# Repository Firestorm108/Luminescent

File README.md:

# Luminescent

A 60W handheld portal gun based on industrial surplus I acquired off eBay. I use a very high power laser diode array that is from industrial laser modules for purposes like copper treatment. It has a fully custom board that manages constant current regulation and battery management.
It fits inside a 3D printable portal gun with a voltmeter, safety, and trigger. 

<h1>Laser Safety</h1>

** Make sure to ALWAYS buy laser goggles from a reputable brand and with properly rated specifications. **

** Lasers are extremely dangerous and you should never look at them directly and always wear proper safety goggles. **

** I am not responsible for any damage caused from irresponsibly using lasers. ** 

**General Tips for Working with Lasers:**

* The glasses that come with lasers are NOT safe, and will not protect your eyes.

* Lasers over 5mW require proper laser goggles, 5mW is still dangerous however the blink reflex protects you in most cases.

* Cutting with lasers releases fumes which need to be filtered or ventilated to a window, preferably both.

* An enclosure is the BARE minimum for safety along with properly rated laser goggles.

* Do LOTS of research before working with lasers. Diode lasers need to be treated very carefully especially.

# Pictures

# Bill of Materials

| Item                                      | Price | Link                                                               |
| ----------------------------------------- | ----: | ------------------------------------------------------------------ |
| JLCPCB + Assembly + Shipping              |  $170 | [JLCPCB](https://jlcpcb.com)                                       |
| Blue Laser Diode Array                    |  $140 | [eBay](https://www.ebay.com/itm/117338976687)                      |
| LM338                                     |    $6 | [AliExpress](https://www.aliexpress.us/item/3256809812350367.html) |
| Toggle Switches                           |    $3 | [AliExpress](https://www.aliexpress.us/item/3256805504896607.html) |
| 0.625 ohm Resistors                       |    $2 | [AliExpress](https://www.aliexpress.us/item/3256809808109885.html) |
| Mini Voltmeter                            |    $2 | [AliExpress](https://www.aliexpress.us/item/3256807826514920.html) |
| Lithium Ion Battery + Charger (XT60 - DC) |   $32 | [AliExpress](https://www.aliexpress.us/item/3256811403962565.html) |
| Cooling Fans + Heatsink                   |   $12 | [AliExpress](https://www.aliexpress.us/item/2251832856177807.html) |
| Collimating Laser Lenses                  |   $40 | [eBay](https://www.ebay.com/itm/236181151103)                      |

## Cost Summary

|              |   Amount |
| ------------ | -------: |
| **Subtotal** | **$407** |
| **Tax**      |  **$43** |
| **Total**    | **$450** |

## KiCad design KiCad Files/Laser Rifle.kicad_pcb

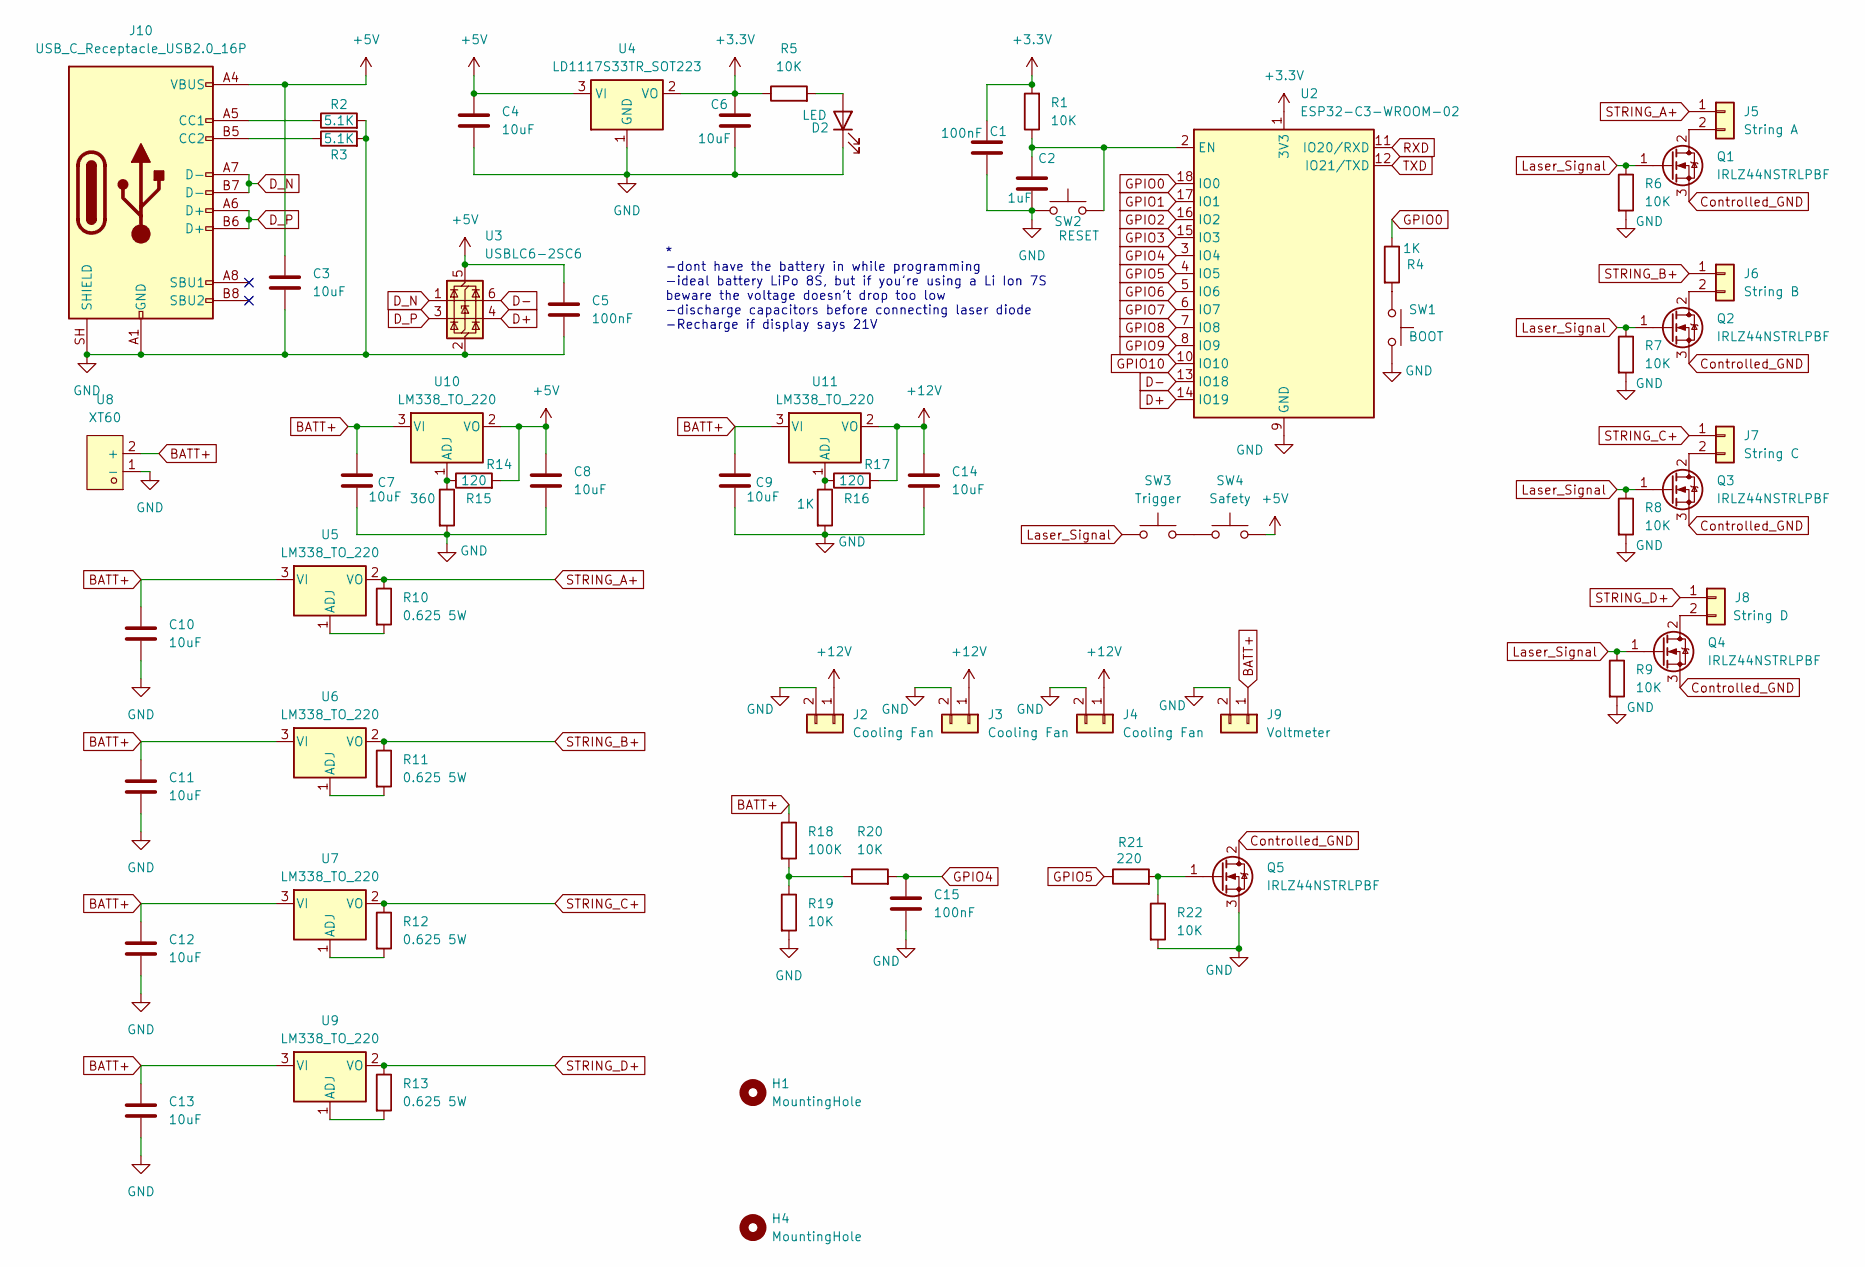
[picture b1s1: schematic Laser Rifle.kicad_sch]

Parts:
C1, C5, C15: 100nF; C_0603_1608Metric
C2: 1uF; C_0603_1608Metric
C3, C4, C6, C7, C8, C9, C10, C11, C12, C13, C14: 10uF; C_0603_1608Metric
D2: LED; LED_0805_2012Metric
H1, H4: MountingHole; MountingHole_3.2mm_M3
J2, J3, J4: Cooling Fan; PinHeader_1x02_P2.54mm_Vertical
J5: String A; CONN-TH_P10.16_KF135T-10.16-2P
J6: String B; CONN-TH_P10.16_KF135T-10.16-2P
J7: String C; CONN-TH_P10.16_KF135T-10.16-2P
J8: String D; CONN-TH_P10.16_KF135T-10.16-2P
J9: Voltmeter; PinHeader_1x02_P2.54mm_Vertical
J10: USB_C_Receptacle_USB2.0_16P; USB_C_Receptacle_HRO_TYPE-C-31-M-12
Q1, Q2, Q3, Q4, Q5: IRLZ44NSTRLPBF; TO-263-2
R1, R5, R6, R7, R8, R9, R19, R20, R22: 10K; R_0603_1608Metric
R2, R3: 5.1K; R_0603_1608Metric
R4, R16: 1K; R_0603_1608Metric
R10, R11, R12, R13: 0.625 5W; R_Box_L14.0mm_W5.0mm_P9.00mm
R14, R17: 120; R_0603_1608Metric
R15: 360; R_0603_1608Metric
R18: 100K; R_0603_1608Metric
R21: 220; R_0603_1608Metric
SW1: BOOT; SW_Push_SPST_NO_Alps_SKRK
SW2: RESET; SW_Push_SPST_NO_Alps_SKRK
SW3: Trigger; PinHeader_1x02_P2.54mm_Vertical
SW4: Safety; PinHeader_1x02_P2.54mm_Vertical
U2: ESP32-C3-WROOM-02
U3: USBLC6-2SC6; SOT-23-6
U4: LD1117S33TR_SOT223; SOT-223-3_TabPin2
U5, U6, U7, U9, U10, U11: LM338_TO_220; TO-220-3_Vertical
U8: XT60; CONN-TH_XT60; MPN XT60-M.; LCSC Part C98733

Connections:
+3.3V: C1.1, C6.1, R1.2, R5.1, U2.1 (3V3), U4.2 (VO)
+5V: C3.1, C4.1, C5.1, C8.1, J10.A4 (VBUS), J10.A9 (VBUS), J10.B4 (VBUS), J10.B9 (VBUS), R14.2, SW4.2, U3.5 (VBUS), U4.3 (VI), U10.2 (VO)
+12V: C14.1, J2.1, J3.1, J4.1, R17.2, U11.2 (VO)
BATT+: C7.1, C9.1, C10.1, C11.1, C12.1, C13.1, J9.1, R18.1, U5.3 (VI), U6.3 (VI), U7.3 (VI), U8.2 (+), U9.3 (VI), U10.3 (VI), U11.3 (VI)
Controlled_GND: Q1.3 (S), Q2.3 (S), Q3.3 (S), Q4.3 (S), Q5.2 (D)
D+: U2.14 (IO19), U3.4 (I/O2)
D-: U2.13 (IO18), U3.6 (I/O1)
D_N: J10.A7 (D-), J10.B7 (D-), U3.1 (I/O1)
D_P: J10.A6 (D+), J10.B6 (D+), U3.3 (I/O2)
GND: C1.2, C2.2, C3.2, C4.2, C5.2, C6.2, C7.2, C8.2, C9.2, C10.2, C11.2, C12.2, C13.2, C14.2, C15.2, D2.1 (K), J2.2, J3.2, J4.2, J9.2, J10.A1 (GND), J10.A12 (GND), J10.B1 (GND), J10.B12 (GND), J10.SH (SHIELD), Q5.3 (S), R2.2, R3.2, R6.2, R7.2, R8.2, R9.2, R15.2, R16.2, R19.2, R22.2, SW1.2, SW2.1, U2.9 (GND), U2.19 (GND), U3.2 (GND), U4.1 (GND), U8.1 (-)
GPIO0: R4.1, U2.18 (IO0)
GPIO1: U2.17 (IO1)
GPIO2: U2.16 (IO2)
GPIO3: U2.15 (IO3)
GPIO4: C15.1, R20.2, U2.3 (IO4)
GPIO5: R21.1, U2.4 (IO5)
GPIO6: U2.5 (IO6)
GPIO7: U2.6 (IO7)
GPIO8: U2.7 (IO8)
GPIO9: U2.8 (IO9)
GPIO10: U2.10 (IO10)
Laser_Signal: Q1.1 (G), Q2.1 (G), Q3.1 (G), Q4.1 (G), R6.1, R7.1, R8.1, R9.1, SW3.1
unnamed: D2.2 (A), R5.2
unnamed: J5.2, Q1.2 (D)
unnamed: J6.2, Q2.2 (D)
unnamed: J7.2, Q3.2 (D)
unnamed: J8.2, Q4.2 (D)
unnamed: J10.A5 (CC1), R2.1
unnamed: J10.B5 (CC2), R3.1
unnamed: Q5.1 (G), R21.2, R22.1
unnamed: R4.2, SW1.1
unnamed: R18.2, R19.1, R20.1
unnamed: SW3.2, SW4.1
unnamed: C2.1, R1.1, SW2.2, U2.2 (EN)
unnamed: R10.2, U5.1 (ADJ)
unnamed: R11.2, U6.1 (ADJ)
unnamed: R12.2, U7.1 (ADJ)
unnamed: R13.2, U9.1 (ADJ)
unnamed: R14.1, R15.1, U10.1 (ADJ)
unnamed: R16.1, R17.1, U11.1 (ADJ)
RXD: U2.11 (IO20/RXD)
STRING_A+: J5.1, R10.1, U5.2 (VO)
STRING_B+: J6.1, R11.1, U6.2 (VO)
STRING_C+: J7.1, R12.1, U7.2 (VO)
STRING_D+: J8.1, R13.1, U9.2 (VO)
TXD: U2.12 (IO21/TXD)

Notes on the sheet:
* -dont have the battery in while programming -ideal battery LiPo 8S, but if you're using a Li Ion 7S beware the voltage doesn't drop too low -discharge capacitors before connecting laser diode -Recharge if display says 21V

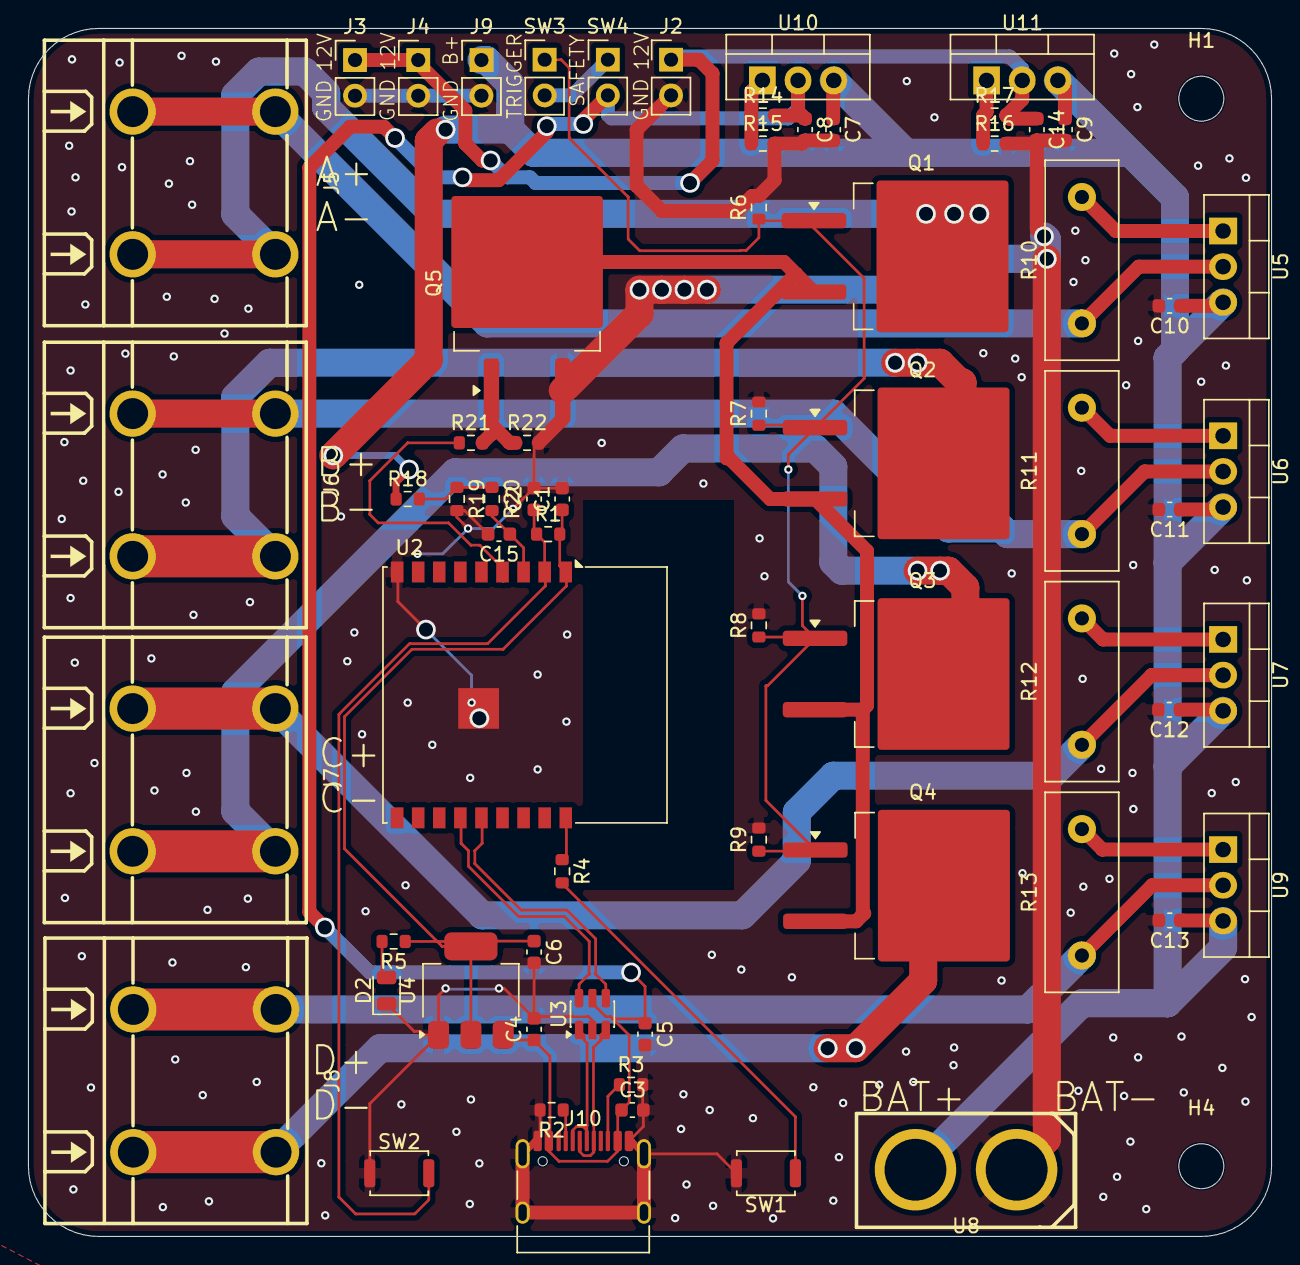
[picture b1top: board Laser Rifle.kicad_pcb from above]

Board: 2 copper layers, 88.5 x 86.0 mm, 68 parts (0 on the bottom side), 36 nets.
